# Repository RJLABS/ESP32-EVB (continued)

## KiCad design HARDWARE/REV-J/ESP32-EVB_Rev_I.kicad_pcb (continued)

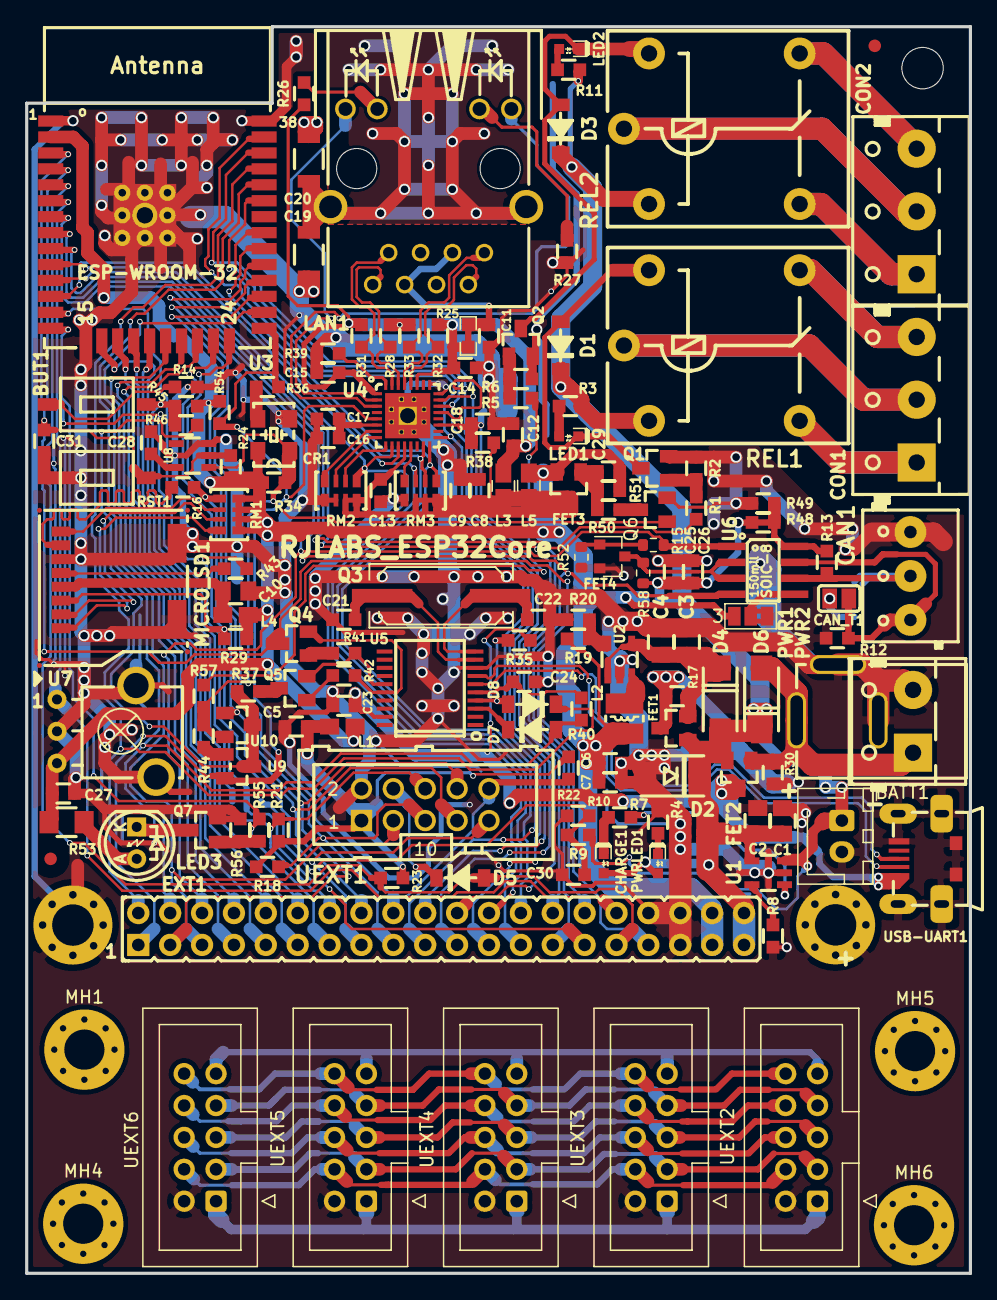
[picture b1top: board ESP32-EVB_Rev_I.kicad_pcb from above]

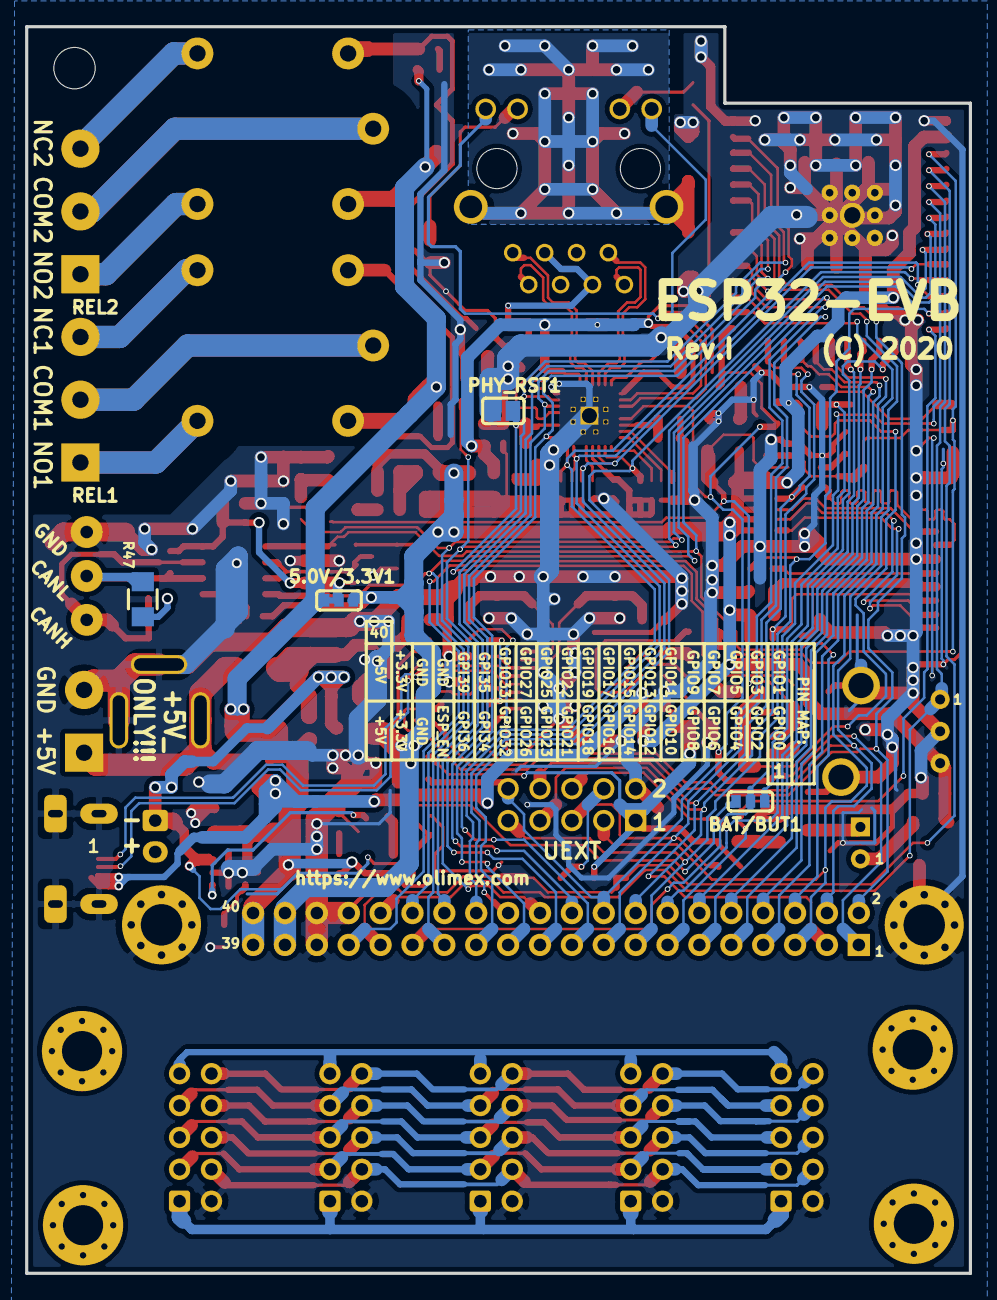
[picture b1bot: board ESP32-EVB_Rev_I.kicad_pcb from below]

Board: 2 copper layers, 75.2 x 99.3 mm, 166 parts (4 on the bottom side), 126 nets.

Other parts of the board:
Fid1, Fid3: Fiducial1x3
MH1#2: Mounting_hole_Shield_3.3mm; Mounting_hole_3.3mm

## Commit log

2021-08-31 update modbus version
2021-09-08 Update 434121043836 (rev1).stp, 5040771891.stp, and 173 more files...
2021-09-09 Update ESP32-EVB_Rev_I-cache.lib, ESP32-EVB_Rev_I.kicad_pcb, and 3 more files...
2021-09-15 fix auto control flow modbus
2021-09-15 done modbus 485
2021-09-15 re-position micro usb port
2021-09-15 Update ESP32-EVB_Rev_I-cache.lib, ESP32-EVB_Rev_I.kicad_pcb, and 4 more files...
2021-09-15 Update fp-info-cache
2021-09-16 re-position usb port+bat conector
2021-09-16 done add 5 extension UEXT
2021-09-16 add 3d header 20pin
2021-09-16 fix UEXT extention
2021-09-16 add hole mount splitter
2021-09-16 fix hole position
2021-09-16 minor update spliter
2021-09-17 update carging controller
2021-09-17 re-Route batrai charging
2021-09-20 fix bat carging route
